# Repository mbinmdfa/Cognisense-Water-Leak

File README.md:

# Cognisense-Water-Leak
Cognisense Water Leak PCB design

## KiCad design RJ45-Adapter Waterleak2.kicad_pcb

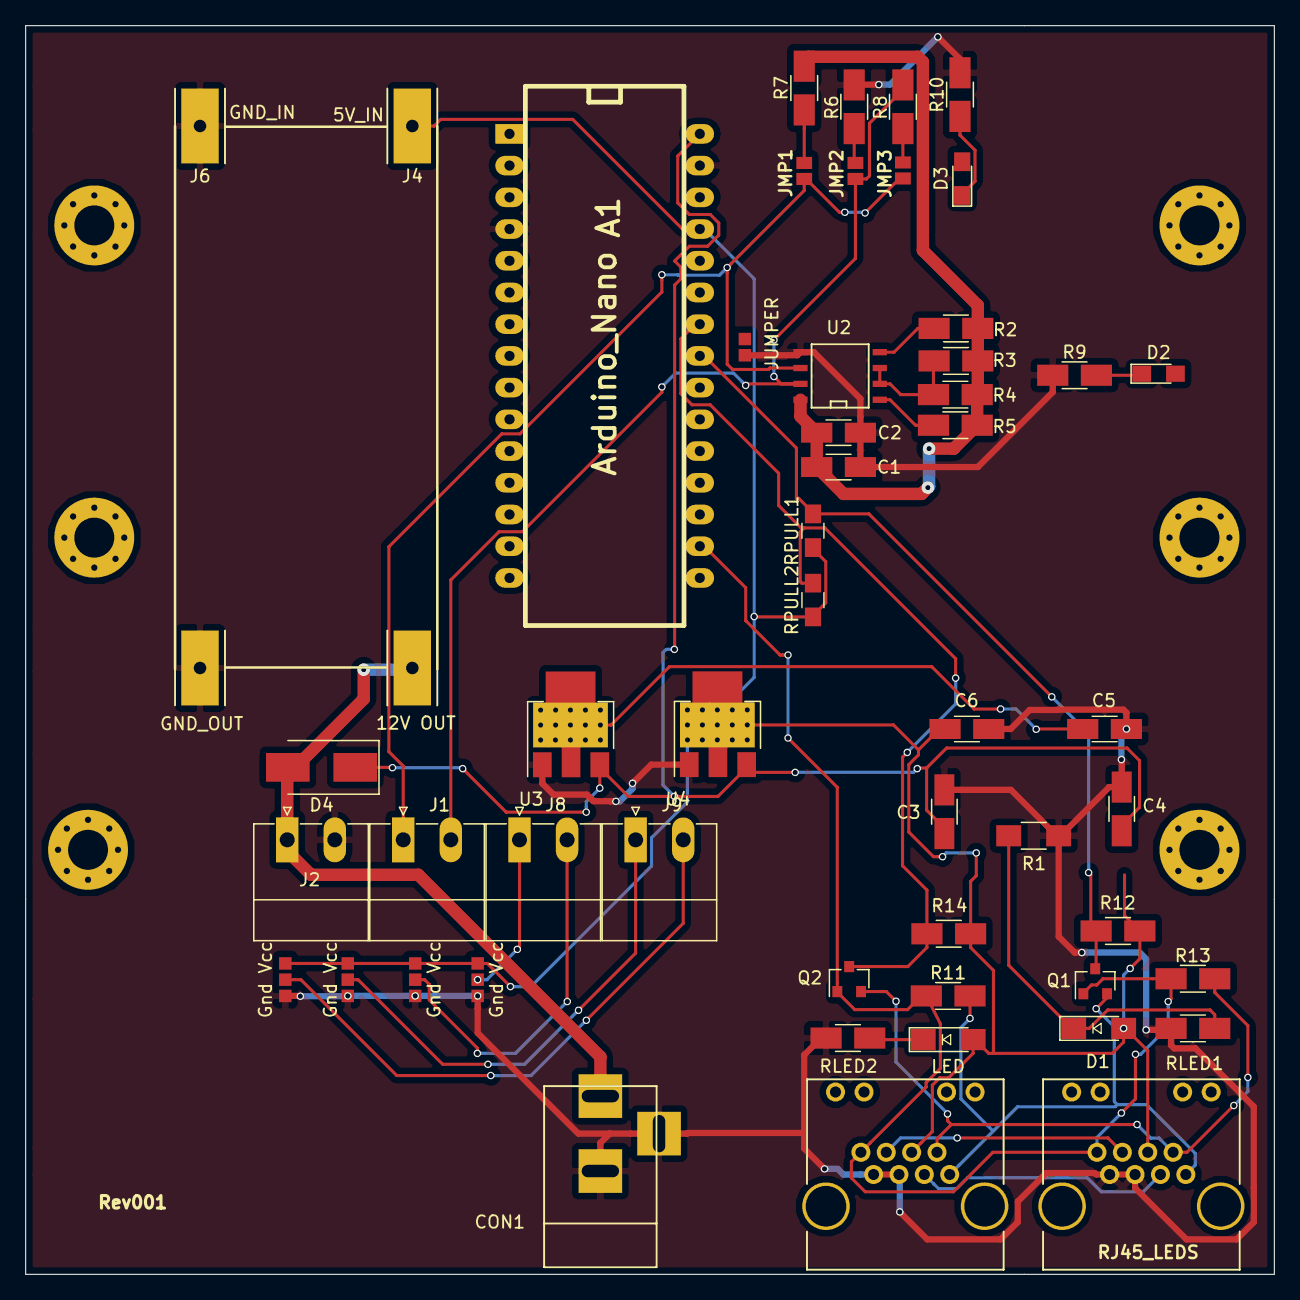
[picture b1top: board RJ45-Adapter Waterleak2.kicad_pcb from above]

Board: 2 copper layers, 100.0 x 100.0 mm, 54 parts (0 on the bottom side), 29 nets.

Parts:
A1: Arduino_Nano; arduino_nano2
C1, C2: C; C_0805_1206_HS
C3, C4, C5, C6: 10uF; C_0805_1206_HS
CON1: BARREL_JACK
D1: LED; LED_1206_HS_with_icon
D2: Rx_LED; LED_0805_HandSoldering
D3: Tx_LED; LED_0805_HandSoldering
D4: D; D_SMB_Handsoldering
GS1: JMP2; GS2
GS2: JMP1; GS2
GS3: JMP3; GS2
J1: A B; PhoenixContact_MC_1,5_2-G-3.81_1x02_P3.81mm_Horizontal
J2: 12V; PhoenixContact_MC_1,5_2-G-3.81_1x02_P3.81mm_Horizontal
J3: 12V OUT; Pads_3x6mm
J4: 5V_IN; Pads_3x6mm
J5: GND_OUT; Pads_3x6mm
J6: GND_IN; Pads_3x6mm
J7, J14: RJ45_LEDS; CONNECTOR_RJ45_RA_TH_LEDS
J8, J9: P2; PhoenixContact_MC_1,5_2-G-3.81_1x02_P3.81mm_Horizontal
JP1, JP2, JP4, JP5: Gnd Vcc; SJ3
JP3: JUMPER; SJ2
LED2: LED; LED_1206_HS_with_icon
Q1, Q2: BSS138; SOT-23
R1: R; R_1206_HandSoldering
R2, R3, R4, R5, R9, R10: R; R_08051206_HS
R6, R7: 4K7; R_08051206_HS
R8: 120; R_08051206_HS
R11, R12, R13, R14: 10K; R_08051206_HS
RLED1, RLED2: 1K; R_08051206_HS
RPULL1, RPULL2: 4.7K; R_0805_HandSoldering
U2: MAX485; SOIC-8-N
U3: 1117-3.3V; SOT-223_15vias
U4: 1117-5V; SOT-223_15vias

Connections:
+3V3: A1.17, J7.8, J14.8, Q1.1, Q2.1, R11.1, R13.1
+5V: A1.27, C6.1, D1.2, J4.1, J7.4, J14.4, JP1.3, JP2.3, JP4.3, JP5.3, LED2.2, R12.1, R14.1, RPULL1.1, RPULL2.1, U4.2
/2: J7.2, J14.2, Q2.2, R13.2
/3: J7.3, J14.3
/3.3V: C5.1, U3.2
/6: J7.6, J14.6
/12V: CON1.1, D4.2, J2.1, J3.1
/DI: R2.2, U2.4
/REDE: R3.2, R4.2, U2.2, U2.3
/RO: R5.2, U2.1
/SCL-HV: A1.24, Q2.3, R14.2, RPULL2.2
/SDA-HV: A1.23, Q1.3, R12.2, RPULL1.2
/SDA-LV: J7.1, J14.1, Q1.2, R11.2
/VIN: A1.30, C3.1, C4.1, D4.1, U3.3, U4.3
GND: A1.4, A1.29, C1.1, C2.1, C3.2, C4.2, C5.2, C6.2, CON1.2, CON1.3, J2.2, J5.1, J6.1, J7.5, J7.7, J14.5, J14.7, JP1.1, JP2.1, JP3.1, JP4.1, JP5.1, R1.1, R6.1, R9.1, R10.2, RLED1.1, RLED2.1, U2.5, U3.1, U4.1
unnamed: D1.1, R1.2, RLED1.2
unnamed: D2.1, R9.2
unnamed: D3.1, R10.1
unnamed: GS1.1, J1.2, R8.2, U2.7
unnamed: GS1.2, R6.2
unnamed: GS2.1, GS3.2, J1.1, U2.6
unnamed: GS2.2, R7.1
unnamed: GS3.1, R8.1
unnamed: J8.1, JP4.2
unnamed: J8.2, JP5.2
unnamed: J9.1, JP2.2
unnamed: J9.2, JP1.2
unnamed: LED2.1, RLED2.2
VCC: C1.2, C2.2, R2.1, R3.1, R4.1, R5.1, R7.2, U2.8
